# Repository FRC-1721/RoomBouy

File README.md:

# RoomBouy

This repo contains all the firmware and hardware for the RoomBouy.

If you're looking for the latest docs/builds, see our [Releases Page](https://github.com/FRC-1721/RoomBouy/releases).

# Getting Started

First, clone this repo (and optionally checkout a branch)

```shell
git clone https://github.com/FRC-1721/RoomBouy.git
cd RoomBouy
```

# Init Submodules

Some libraries and resources are included as submodules, run the following
command to initialize them before opening the main sch

(If you get a missing library error, make sure to do this)

```shell
git submodule update --init --recursive
```

## Project Layout

If you want to use this project template for yourself, you can find it [here!](https://github.com/KenwoodFox/Project-Template)

# Thanks

## KiCAD Templates

Thanks [devbisme](https://github.com/devbisme) for [RPI Hat Template](https://github.com/devbisme/RPi_Hat_Template)!

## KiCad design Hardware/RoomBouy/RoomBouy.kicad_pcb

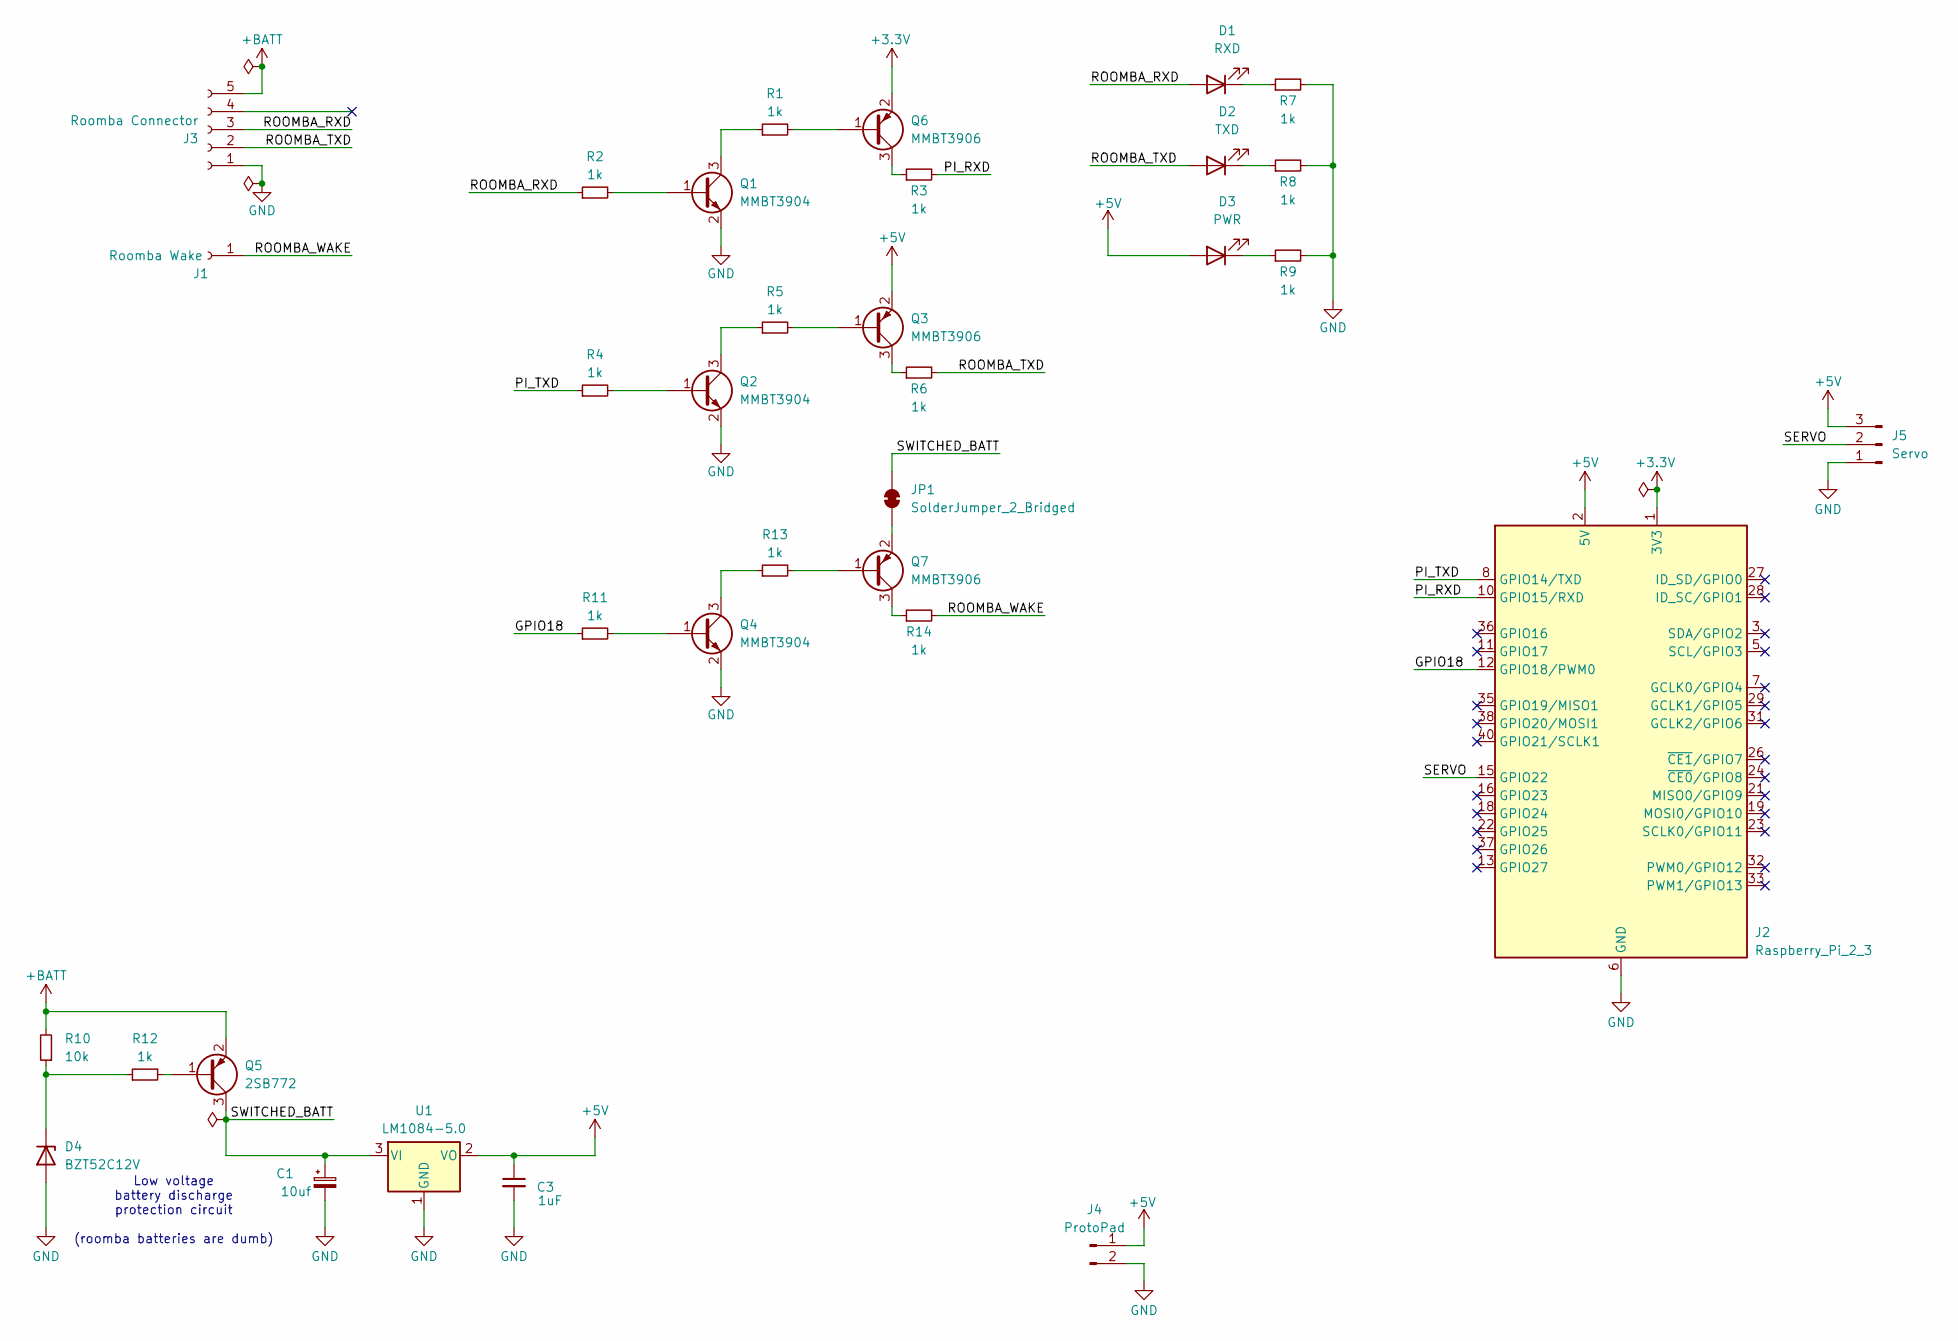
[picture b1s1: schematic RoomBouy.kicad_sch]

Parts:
C1: 10uf; CP_Elec_4x3
C3: 1uF; C_0805_2012Metric
D1: RXD; LED_0805_2012Metric
D2: TXD; LED_0805_2012Metric
D3: PWR; LED_0805_2012Metric
D4: BZT52C12V; D_SOD-123; LCSC# C5182293
J1: Roomba Wake; SolderWire-0.25sqmm_1x01_D0.65mm_OD1.7mm_Relief
J2: Raspberry_Pi_2_3; RPI_Hat_B+
J3: Roomba Connector; SolderWire-0.25sqmm_1x05_P4.2mm_D0.65mm_OD1.7mm_Relief
J4: ProtoPad
J5: Servo; JST_EH_S3B-EH_1x03_P2.50mm_Horizontal
JP1: SolderJumper_2_Bridged; SolderJumper-2_P1.3mm_Bridged2Bar_RoundedPad1.0x1.5mm
Q1, Q2, Q4: MMBT3904; SOT-23
Q3, Q6, Q7: MMBT3906; SOT-23
Q5: 2SB772; TO-252-2; LCSC# C3008133
R1, R2, R3, R4, R5, R6, R7, R8, R9, R11, R12, R13, R14: 1k; R_0805_2012Metric
R10: 10k; R_0805_2012Metric
U1: LM1084-5.0; TO-220-3_Horizontal_TabDown

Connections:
+3.3V: J2.1 (3V3), J2.17 (3V3), Q6.2 (E)
+5V: C3.1, D3.2 (A), J2.2 (5V), J2.4 (5V), J4.1, J5.3, Q3.2 (E), U1.2 (VO)
+BATT: J3.5, Q5.2 (E), R10.2
/GPIO18: J2.12 (GPIO18/PWM0), R11.1
/PI_RXD: J2.10 (GPIO15/RXD), R3.2
/PI_TXD: J2.8 (GPIO14/TXD), R4.1
/ROOMBA_RXD: D1.2 (A), J3.3, R2.1
/ROOMBA_TXD: D2.2 (A), J3.2, R6.2
/ROOMBA_WAKE: J1.1, R14.2
/SERVO: J2.15 (GPIO22), J5.2
/SWITCHED_BATT: C1.1, JP1.2 (B), Q5.3 (C), U1.3 (VI)
GND: C1.2, C3.2, D4.2 (A), J2.6 (GND), J2.9 (GND), J2.14 (GND), J2.20 (GND), J2.25 (GND), J2.30 (GND), J2.34 (GND), J2.39 (GND), J3.1, J4.2, J5.1, Q1.2 (E), Q2.2 (E), Q4.2 (E), R7.2, R8.2, R9.2, U1.1 (GND)
unnamed: D1.1 (K), R7.1
unnamed: D2.1 (K), R8.1
unnamed: D3.1 (K), R9.1
unnamed: D4.1 (K), R10.1, R12.1
unnamed: JP1.1 (A), Q7.2 (E)
unnamed: Q1.1 (B), R2.2
unnamed: Q1.3 (C), R1.1
unnamed: Q2.1 (B), R4.2
unnamed: Q2.3 (C), R5.1
unnamed: Q3.1 (B), R5.2
unnamed: Q3.3 (C), R6.1
unnamed: Q4.1 (B), R11.2
unnamed: Q4.3 (C), R13.1
unnamed: Q5.1 (B), R12.2
unnamed: Q6.1 (B), R1.2
unnamed: Q6.3 (C), R3.1
unnamed: Q7.1 (B), R13.2
unnamed: Q7.3 (C), R14.1

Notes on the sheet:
Low voltage battery discharge protection circuit (roomba batteries are dumb)

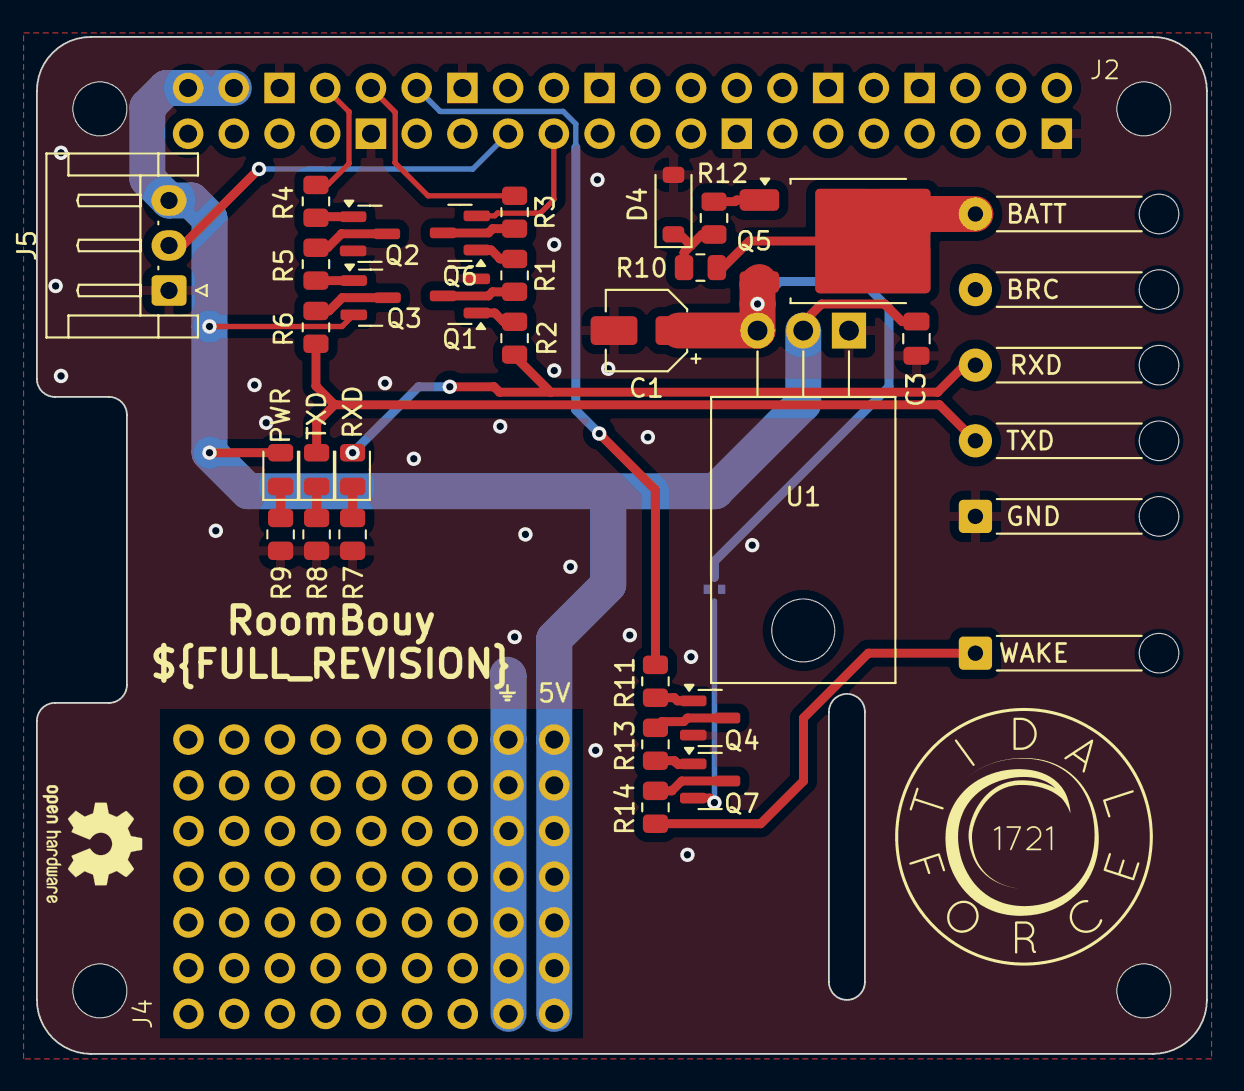
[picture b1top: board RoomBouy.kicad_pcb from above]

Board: 2 copper layers, 65.0 x 56.5 mm, 34 parts (1 on the bottom side), 30 nets.

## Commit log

2024-08-15 Init to commit it!
2024-08-15 Add upstream libs and kicad templates
2024-08-15 Use our own fork
2024-08-15 Bump to kicad8
2024-08-15 Clean sheet
2024-08-15 Add internal libs, do full board layout, bump k8 and fix ERC
2024-08-15 Fix config for k8
2024-08-15 Fix config for k8 (again)
2024-08-15 Fix DRC
2024-08-15 Fix revision tag
2024-08-22 Add a low-voltage protection circuit (to protect against over-discharging roomba batteries
2024-08-22 Fix switched power
2024-08-22 Bump zoom
2024-09-05 Add stencil
2024-10-20 Bump rpi_hat_template
    Co-Authored By: @devbisme
2025-06-24 Bump to new ver
2025-06-24 rename txd thru all
2025-06-24 Bump to new ver ci/cd
2025-06-24 Bump cache and kibot
